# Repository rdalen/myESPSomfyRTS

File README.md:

# myESPSomfyRTS

A DIY Somfy RTS controller for my SunRain Awning/Shade, based on the open-source [ESPSomfyRTS](https://github.com/rstrouse/ESPSomfy-RTS) project.

The controller uses an ESP32 together with a CC1101 433 MHz RF transceiver and integrates with my Home Assistant and Node-RED setup.

<p align="center"><i>Architecture diagram</i></p>

## How It Works

- **Hardware:** ESP32 microcontroller paired with a CC1101 radio transceiver module.
- **Communication:** Connects to my home Wi-Fi network and sends 433 MHz radio signals compatible with the Somfy RTS (Radio Technology Somfy) protocol.
- **Local Operation:** ESPSomfyRTS provides a built-in web interface for controlling the shade directly from a phone or computer.
- **Smart Home Integration:** The controller integrates with Home Assistant and Node-RED for automation and monitoring.
- **Position Tracking:** Tracks the shade position independently of the physical Somfy remote.

For the firmware, general wiring information and ESPSomfyRTS documentation, see the official [ESPSomfyRTS project](https://github.com/rstrouse/ESPSomfy-RTS).

An instruction video is available on [YouTube](https://www.youtube.com/watch?v=1acVJ0xWJgs).

---

## Repository Contents

This repository contains the files specific to my implementation:

- 📁 **[KiCad](./KiCad)** — Schematic and PCB design files
- 📁 **[nodeRed](./nodeRed)** — Node-RED flows used for control, monitoring and automation

The ESP32 firmware itself is based on the [ESPSomfyRTS](https://github.com/rstrouse/ESPSomfy-RTS) project.

---

## CC1101 433 MHz RF Transceiver

My version of the CC1101-based module (E07-M1101D-SMA) exposes only a single GDO line, while ESPSomfyRTS is often configured with separate RX and TX signal pins.

By assigning both RX and TX to the same GPIO, ESPSomfyRTS can use the single GDO line for both receiving and transmitting.

The GPIO configuration with the Seeed Studio XIAO ESP32-S3 is:

- **RX Pin = GPIO3**
- **TX Pin = GPIO3** ← same GPIO as RX

### ESP32-S3 XIAO

Pin connections between the CC1101 module and the XIAO ESP32-S3:

| CC1101 Pin | Description | ESP Signal | ESP Pin |
| --- | --- | --- | --- |
| 1 | GND | GND | 13 |
| 2 | VCC | 3V3 | 12 |
| 3 | GDO0 - RX/TX | GPIO 03 | 3 |
| 4 | CSN | GPIO 06 | 6 |
| 5 | SCK | GPIO 07 | 9 |
| 6 | MOSI | GPIO 09 | 11 |
| 7 | MISO | GPIO 08 | 10 |
| 8 | Not connected | | |

Here is the corresponding ESPSomfyRTS radio configuration:

---

## Schematic & PCB

I designed a small custom PCB for the controller.

The complete KiCad project is available in the **[KiCad](./KiCad)** folder.

Before ordering, I panelized the PCB design so I have several boards available for experimenting with and sharing.

---

## Enclosure

Finally, I "Boxified" an enclosure for the controller using my [Boxify Parametric Electronics Enclosure Framework](https://cad.onshape.com/documents/2429cd535c2c818681c446f4/w/762b6c313c33766c159c34b3/e/4a0a0d23bcb24ef244694428).

See also my [Boxify Instructable](https://www.instructables.com/-Boxify-a-Parametric-Electronics-Enclosure-Framewo).

The enclosure was then 3D printed.

The STL files are available in the **[Enclosure](./Enclosure)** folder of this repository, so you can print your own enclosure without having to generate the models yourself.

The folder contains the STL files for the box base, lid, adapter plate, and text labels.

---

## Controlling the SunRain Shade

The Somfy motor does not provide a motor-running feedback signal.

I therefore derive the motor-running state from a HomeWizard Energy Socket. The motor uses approximately 200 W while running, making it possible to detect whether the motor is active.

For controlling and monitoring the shade I created a Node-RED dashboard.

The complete Node-RED flow is available in the **[nodeRed](./nodeRed)** folder.

The dashboard allows me to:

- control the shade
- monitor whether the motor is responding
- track the shade position
- detect when the motor is running
- receive a warning when rain is predicted within 30 minutes

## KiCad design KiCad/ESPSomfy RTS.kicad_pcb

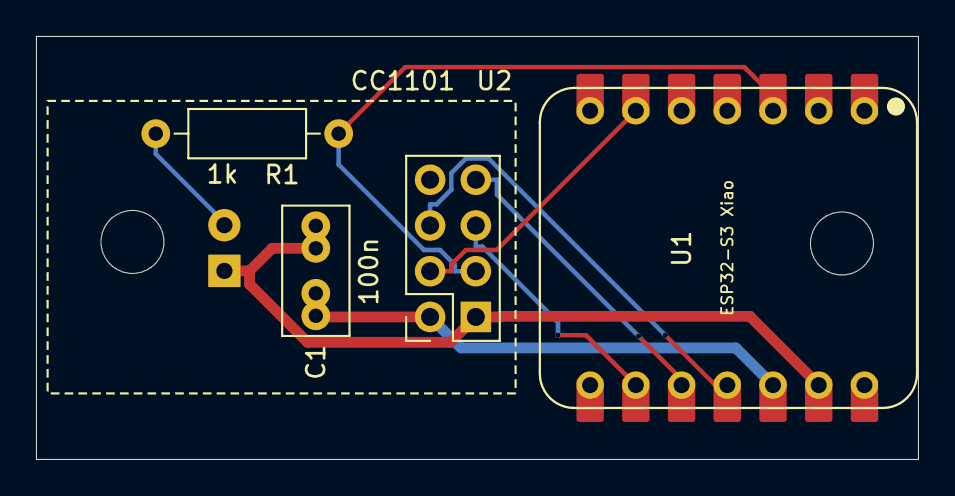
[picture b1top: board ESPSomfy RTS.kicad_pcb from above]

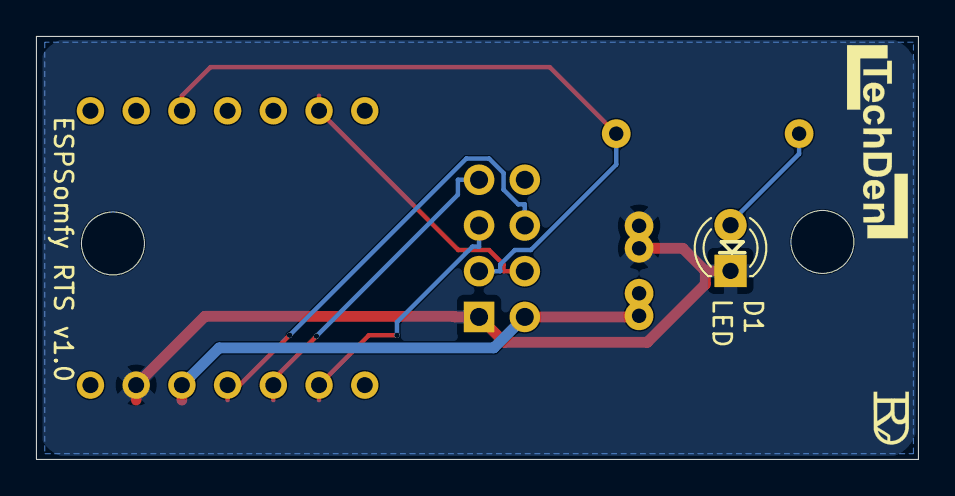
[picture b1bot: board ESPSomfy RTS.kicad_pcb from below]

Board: 2 copper layers, 49.0 x 23.5 mm, 7 parts (3 on the bottom side), 8 nets.

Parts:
C1: 100n; C-Common-THT-P5.08mm
D1: LED; LED-D3.0mm
Logo1: Logo-RvD; LOGO-RvD-inverted-small
Logo2: Logo-TechDen; LOGO-TechDen-inverted
R1: 1k; R-Common-THT-P10.16mm
U1: ESP32-S3 Xiao; MOD-ESP32-S3-XIAO-DIP
U2: CC1101; MOD-CC1101

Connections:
3V3: C1.1 (+), U1.12 (VCC_3V3), U2.2 (VCC)
/GPIO3: R1.1 (+), U1.3 (D2), U2.3 (Tx/Rx)
/GPIO6: U1.6 (D5), U2.4 (CSN)
/GPIO7: U1.9 (D8), U2.5 (SCK)
/GPIO8: U1.10 (D9), U2.7 (MISO)
/GPIO9: U1.11 (D10), U2.6 (MOSI)
unnamed: D1.2 (A+), R1.2 (-)
U-GND: C1.2 (-), D1.1 (K-), U1.13 (GND), U2.1 (GND)

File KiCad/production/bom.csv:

Designator,Footprint,Quantity,Value,LCSC Part #
"C1_8, C1_7, C1_6, C1_5, C1_4, C1_3, C1_2, C1",C-Common-THT-P5.08mm,8,100n,
"D1_8, D1_7, D1_6, D1_5, D1_4, D1_3, D1_2, D1",LED-D3.0mm,8,LED,
"LOGO1_8, LOGO1_7, LOGO1_6, LOGO1_5, LOGO1_4, LOGO1_3, LOGO1_2, LOGO1",LOGO-RvD-inverted-small,8,Logo-RvD,
"LOGO2_8, LOGO2_7, LOGO2_6, LOGO2_5, LOGO2_4, LOGO2_3, LOGO2_2, LOGO2",LOGO-TechDen-inverted,8,Logo-TechDen,
"R1_8, R1_7, R1_6, R1_5, R1_4, R1_3, R1_2, R1",R-Common-THT-P10.16mm,8,1k,
"U1_8, U1_7, U1_6, U1_5, U1_4, U1_3, U1_2, U1",MOD-ESP32-S3-XIAO-DIP,8,ESP32-S3 Xiao,
"U2_8, U2_7, U2_6, U2_5, U2_4, U2_3, U2_2, U2",MOD-CC1101,8,CC1101,

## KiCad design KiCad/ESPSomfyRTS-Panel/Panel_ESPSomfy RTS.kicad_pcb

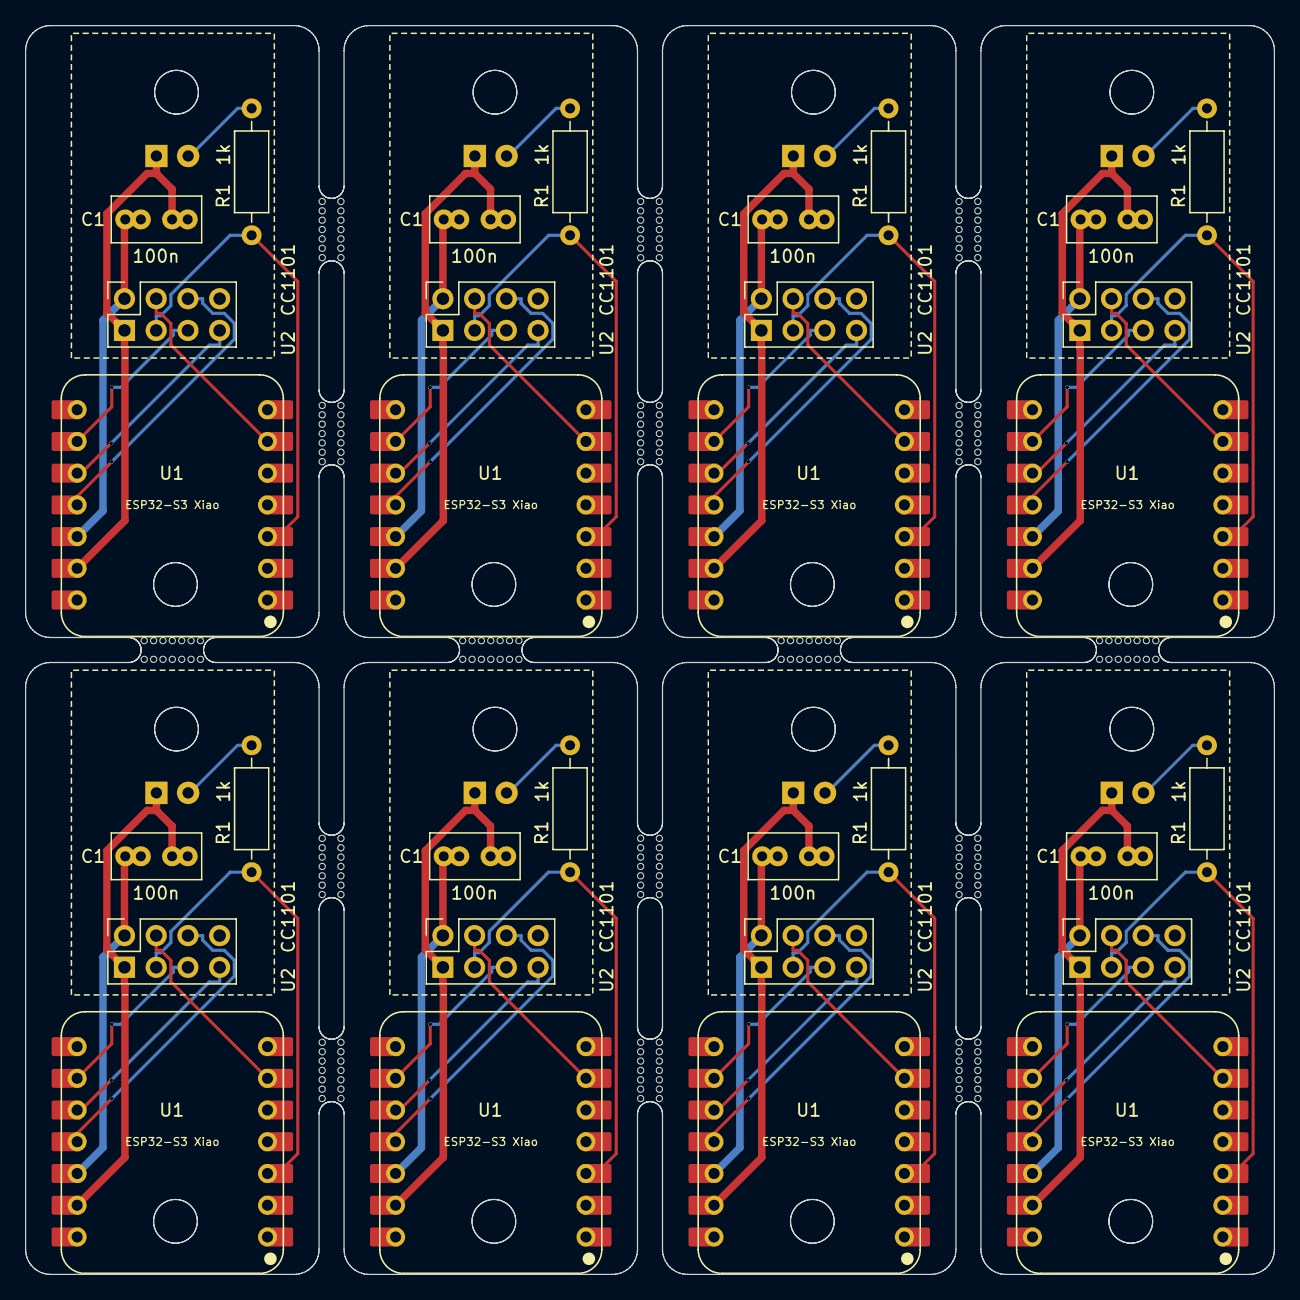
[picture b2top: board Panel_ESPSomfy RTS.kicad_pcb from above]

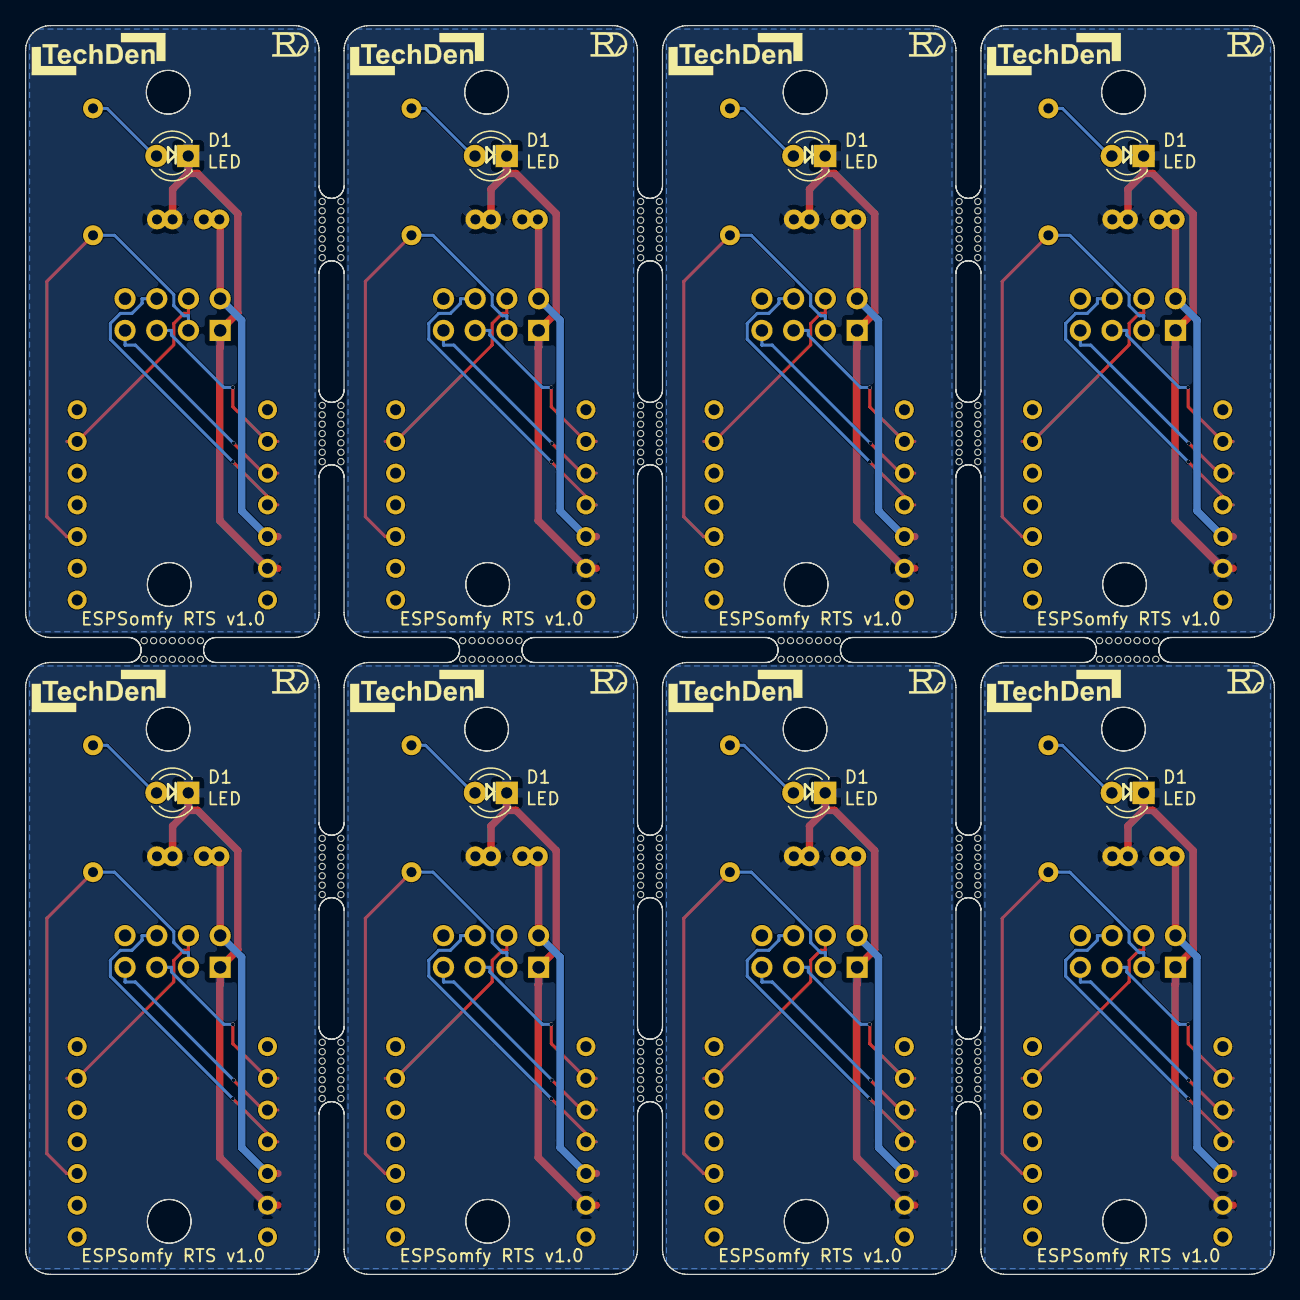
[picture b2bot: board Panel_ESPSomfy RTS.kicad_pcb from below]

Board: 2 copper layers, 100.0 x 100.0 mm, 280 parts (24 on the bottom side), 64 nets.

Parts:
C1, C1#2, C1#3, C1#4, C1#5, C1#6, C1#7, C1#8: 100n; C-Common-THT-P5.08mm
D1, D1#2, D1#3, D1#4, D1#5, D1#6, D1#7, D1#8: LED; LED-D3.0mm
KiKit_MB_1_2, KiKit_MB_1_3, KiKit_MB_1_4, KiKit_MB_1_5, KiKit_MB_1_6, KiKit_MB_1_7, KiKit_MB_1_8, KiKit_MB_2_2, KiKit_MB_2_3, KiKit_MB_2_4, KiKit_MB_2_5, KiKit_MB_2_6, KiKit_MB_2_7, KiKit_MB_2_8, KiKit_MB_3_2, KiKit_MB_3_3, KiKit_MB_3_4, KiKit_MB_3_5, KiKit_MB_3_6, KiKit_MB_3_7, KiKit_MB_3_8, KiKit_MB_4_2, KiKit_MB_4_3, KiKit_MB_4_4, KiKit_MB_4_5, KiKit_MB_4_6, KiKit_MB_4_7, KiKit_MB_4_8, KiKit_MB_5_2, KiKit_MB_5_3, KiKit_MB_5_4, KiKit_MB_5_5, KiKit_MB_5_6, KiKit_MB_5_7, KiKit_MB_5_8, KiKit_MB_6_2, KiKit_MB_6_3, KiKit_MB_6_4, KiKit_MB_6_5, KiKit_MB_6_6, KiKit_MB_6_7, KiKit_MB_6_8, KiKit_MB_7_2, KiKit_MB_7_3, KiKit_MB_7_4, KiKit_MB_7_5, KiKit_MB_7_6, KiKit_MB_7_7, KiKit_MB_7_8, KiKit_MB_8_2, KiKit_MB_8_3, KiKit_MB_8_4, KiKit_MB_8_5, KiKit_MB_8_6, KiKit_MB_8_7, KiKit_MB_8_8, KiKit_MB_9_2, KiKit_MB_9_3, KiKit_MB_9_4, KiKit_MB_9_5, KiKit_MB_9_6, KiKit_MB_9_7, KiKit_MB_9_8, KiKit_MB_10_2, KiKit_MB_10_3, KiKit_MB_10_4, KiKit_MB_10_5, KiKit_MB_10_6, KiKit_MB_10_7, KiKit_MB_10_8, KiKit_MB_11_2, KiKit_MB_11_3, KiKit_MB_11_4, KiKit_MB_11_5, KiKit_MB_11_6, KiKit_MB_11_7, KiKit_MB_11_8, KiKit_MB_12_2, KiKit_MB_12_3, KiKit_MB_12_4, KiKit_MB_12_5, KiKit_MB_12_6, KiKit_MB_12_7, KiKit_MB_12_8, KiKit_MB_13_2, KiKit_MB_13_3, KiKit_MB_13_4, KiKit_MB_13_5, KiKit_MB_13_6, KiKit_MB_13_7, KiKit_MB_13_8, KiKit_MB_14_2, KiKit_MB_14_3, KiKit_MB_14_4, KiKit_MB_14_5, KiKit_MB_14_6, KiKit_MB_14_7, KiKit_MB_14_8, KiKit_MB_15_2, KiKit_MB_15_3, KiKit_MB_15_4, KiKit_MB_15_5, KiKit_MB_15_6, KiKit_MB_15_7, KiKit_MB_15_8, KiKit_MB_16_2, KiKit_MB_16_3, KiKit_MB_16_4, KiKit_MB_16_5, KiKit_MB_16_6, KiKit_MB_16_7, KiKit_MB_16_8, KiKit_MB_17_2, KiKit_MB_17_3, KiKit_MB_17_4, KiKit_MB_17_5, KiKit_MB_17_6, KiKit_MB_17_7, KiKit_MB_17_8, KiKit_MB_18_2, KiKit_MB_18_3, KiKit_MB_18_4, KiKit_MB_18_5, KiKit_MB_18_6, KiKit_MB_18_7, KiKit_MB_18_8, KiKit_MB_19_2, KiKit_MB_19_3, KiKit_MB_19_4, KiKit_MB_19_5, KiKit_MB_19_6, KiKit_MB_19_7, KiKit_MB_19_8, KiKit_MB_20_2, KiKit_MB_20_3, KiKit_MB_20_4, KiKit_MB_20_5, KiKit_MB_20_6, KiKit_MB_20_7, KiKit_MB_20_8, KiKit_MB_21_2, KiKit_MB_21_3, KiKit_MB_21_4, KiKit_MB_21_5, KiKit_MB_21_6, KiKit_MB_21_7, KiKit_MB_21_8, KiKit_MB_22_2, KiKit_MB_22_3, KiKit_MB_22_4, KiKit_MB_22_5, KiKit_MB_22_6, KiKit_MB_22_7, KiKit_MB_22_8, KiKit_MB_23_2, KiKit_MB_23_3, KiKit_MB_23_4, KiKit_MB_23_5, KiKit_MB_23_6, KiKit_MB_23_7, KiKit_MB_23_8, KiKit_MB_24_2, KiKit_MB_24_3, KiKit_MB_24_4, KiKit_MB_24_5, KiKit_MB_24_6, KiKit_MB_24_7, KiKit_MB_24_8, KiKit_MB_25_2, KiKit_MB_25_3, KiKit_MB_25_4, KiKit_MB_25_5, KiKit_MB_25_6, KiKit_MB_25_7, KiKit_MB_25_8, KiKit_MB_26_2, KiKit_MB_26_3, KiKit_MB_26_4, KiKit_MB_26_5, KiKit_MB_26_6, KiKit_MB_26_7, KiKit_MB_26_8, KiKit_MB_27_2, KiKit_MB_27_3, KiKit_MB_27_4, KiKit_MB_27_5, KiKit_MB_27_6, KiKit_MB_27_7, KiKit_MB_27_8, KiKit_MB_28_2, KiKit_MB_28_3, KiKit_MB_28_4, KiKit_MB_28_5, KiKit_MB_28_6, KiKit_MB_28_7, KiKit_MB_28_8, KiKit_MB_29_2, KiKit_MB_29_3, KiKit_MB_29_4, KiKit_MB_29_5, KiKit_MB_29_6, KiKit_MB_29_7, KiKit_MB_29_8, KiKit_MB_30_2, KiKit_MB_30_3, KiKit_MB_30_4, KiKit_MB_30_5, KiKit_MB_30_6, KiKit_MB_30_7, KiKit_MB_30_8, KiKit_MB_31_2, KiKit_MB_31_3, KiKit_MB_31_4, KiKit_MB_31_5, KiKit_MB_31_6, KiKit_MB_31_7, KiKit_MB_31_8, KiKit_MB_32_2, KiKit_MB_32_3, KiKit_MB_32_4, KiKit_MB_32_5, KiKit_MB_32_6, KiKit_MB_32_7, KiKit_MB_32_8: NPTH
Logo1, Logo1#2, Logo1#3, Logo1#4, Logo1#5, Logo1#6, Logo1#7, Logo1#8: Logo-RvD; LOGO-RvD-inverted-small
Logo2, Logo2#2, Logo2#3, Logo2#4, Logo2#5, Logo2#6, Logo2#7, Logo2#8: Logo-TechDen; LOGO-TechDen-inverted
R1, R1#2, R1#3, R1#4, R1#5, R1#6, R1#7, R1#8: 1k; R-Common-THT-P10.16mm
U1, U1#2, U1#3, U1#4, U1#5, U1#6, U1#7, U1#8: ESP32-S3 Xiao; MOD-ESP32-S3-XIAO-DIP
U2, U2#2, U2#3, U2#4, U2#5, U2#6, U2#7, U2#8: CC1101; MOD-CC1101

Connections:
Board_0-3V3: C1.1 (+), U1#5.12 (VCC_3V3), U2#7.2 (VCC)
Board_0-/GPIO3: R1#3.1 (+), U1#5.3 (D2), U2#7.3 (Tx/Rx)
Board_0-/GPIO6: U1#5.6 (D5), U2#7.4 (CSN)
Board_0-/GPIO7: U1#5.9 (D8), U2#7.5 (SCK)
Board_0-/GPIO8: U1#5.10 (D9), U2#7.7 (MISO)
Board_0-/GPIO9: U1#5.11 (D10), U2#7.6 (MOSI)
Board_0-Net-(D1-A+): D1.2 (A+), R1#3.2 (-)
Board_0-U-GND: C1.2 (-), D1.1 (K-), U1#5.13 (GND), U2#7.1 (GND)
Board_1-3V3: C1#4.1 (+), U1#4.12 (VCC_3V3), U2#5.2 (VCC)
Board_1-/GPIO3: R1#5.1 (+), U1#4.3 (D2), U2#5.3 (Tx/Rx)
Board_1-/GPIO6: U1#4.6 (D5), U2#5.4 (CSN)
Board_1-/GPIO7: U1#4.9 (D8), U2#5.5 (SCK)
Board_1-/GPIO8: U1#4.10 (D9), U2#5.7 (MISO)
Board_1-/GPIO9: U1#4.11 (D10), U2#5.6 (MOSI)
Board_1-Net-(D1-A+): D1#5.2 (A+), R1#5.2 (-)
Board_1-U-GND: C1#4.2 (-), D1#5.1 (K-), U1#4.13 (GND), U2#5.1 (GND)
Board_2-3V3: C1#7.1 (+), U1#3.12 (VCC_3V3), U2#4.2 (VCC)
Board_2-/GPIO3: R1#2.1 (+), U1#3.3 (D2), U2#4.3 (Tx/Rx)
Board_2-/GPIO6: U1#3.6 (D5), U2#4.4 (CSN)
Board_2-/GPIO7: U1#3.9 (D8), U2#4.5 (SCK)
Board_2-/GPIO8: U1#3.10 (D9), U2#4.7 (MISO)
Board_2-/GPIO9: U1#3.11 (D10), U2#4.6 (MOSI)
Board_2-Net-(D1-A+): D1#3.2 (A+), R1#2.2 (-)
Board_2-U-GND: C1#7.2 (-), D1#3.1 (K-), U1#3.13 (GND), U2#4.1 (GND)
Board_3-3V3: C1#8.1 (+), U1#6.12 (VCC_3V3), U2#6.2 (VCC)
Board_3-/GPIO3: R1#7.1 (+), U1#6.3 (D2), U2#6.3 (Tx/Rx)
Board_3-/GPIO6: U1#6.6 (D5), U2#6.4 (CSN)
Board_3-/GPIO7: U1#6.9 (D8), U2#6.5 (SCK)
Board_3-/GPIO8: U1#6.10 (D9), U2#6.7 (MISO)
Board_3-/GPIO9: U1#6.11 (D10), U2#6.6 (MOSI)
Board_3-Net-(D1-A+): D1#4.2 (A+), R1#7.2 (-)
Board_3-U-GND: C1#8.2 (-), D1#4.1 (K-), U1#6.13 (GND), U2#6.1 (GND)
Board_4-3V3: C1#5.1 (+), U1#2.12 (VCC_3V3), U2.2 (VCC)
Board_4-/GPIO3: R1.1 (+), U1#2.3 (D2), U2.3 (Tx/Rx)
Board_4-/GPIO6: U1#2.6 (D5), U2.4 (CSN)
Board_4-/GPIO7: U1#2.9 (D8), U2.5 (SCK)
Board_4-/GPIO8: U1#2.10 (D9), U2.7 (MISO)
Board_4-/GPIO9: U1#2.11 (D10), U2.6 (MOSI)
Board_4-Net-(D1-A+): D1#7.2 (A+), R1.2 (-)
Board_4-U-GND: C1#5.2 (-), D1#7.1 (K-), U1#2.13 (GND), U2.1 (GND)
Board_5-3V3: C1#2.1 (+), U1#8.12 (VCC_3V3), U2#3.2 (VCC)
Board_5-/GPIO3: R1#8.1 (+), U1#8.3 (D2), U2#3.3 (Tx/Rx)
Board_5-/GPIO6: U1#8.6 (D5), U2#3.4 (CSN)
Board_5-/GPIO7: U1#8.9 (D8), U2#3.5 (SCK)
Board_5-/GPIO8: U1#8.10 (D9), U2#3.7 (MISO)
Board_5-/GPIO9: U1#8.11 (D10), U2#3.6 (MOSI)
Board_5-Net-(D1-A+): D1#8.2 (A+), R1#8.2 (-)
Board_5-U-GND: C1#2.2 (-), D1#8.1 (K-), U1#8.13 (GND), U2#3.1 (GND)
Board_6-3V3: C1#6.1 (+), U1.12 (VCC_3V3), U2#2.2 (VCC)
Board_6-/GPIO3: R1#6.1 (+), U1.3 (D2), U2#2.3 (Tx/Rx)
Board_6-/GPIO6: U1.6 (D5), U2#2.4 (CSN)
Board_6-/GPIO7: U1.9 (D8), U2#2.5 (SCK)
Board_6-/GPIO8: U1.10 (D9), U2#2.7 (MISO)
Board_6-/GPIO9: U1.11 (D10), U2#2.6 (MOSI)
Board_6-Net-(D1-A+): D1#6.2 (A+), R1#6.2 (-)
Board_6-U-GND: C1#6.2 (-), D1#6.1 (K-), U1.13 (GND), U2#2.1 (GND)
Board_7-3V3: C1#3.1 (+), U1#7.12 (VCC_3V3), U2#8.2 (VCC)
Board_7-/GPIO3: R1#4.1 (+), U1#7.3 (D2), U2#8.3 (Tx/Rx)
Board_7-/GPIO6: U1#7.6 (D5), U2#8.4 (CSN)
Board_7-/GPIO7: U1#7.9 (D8), U2#8.5 (SCK)
Board_7-/GPIO8: U1#7.10 (D9), U2#8.7 (MISO)
Board_7-/GPIO9: U1#7.11 (D10), U2#8.6 (MOSI)
Board_7-Net-(D1-A+): D1#2.2 (A+), R1#4.2 (-)
Board_7-U-GND: C1#3.2 (-), D1#2.1 (K-), U1#7.13 (GND), U2#8.1 (GND)
